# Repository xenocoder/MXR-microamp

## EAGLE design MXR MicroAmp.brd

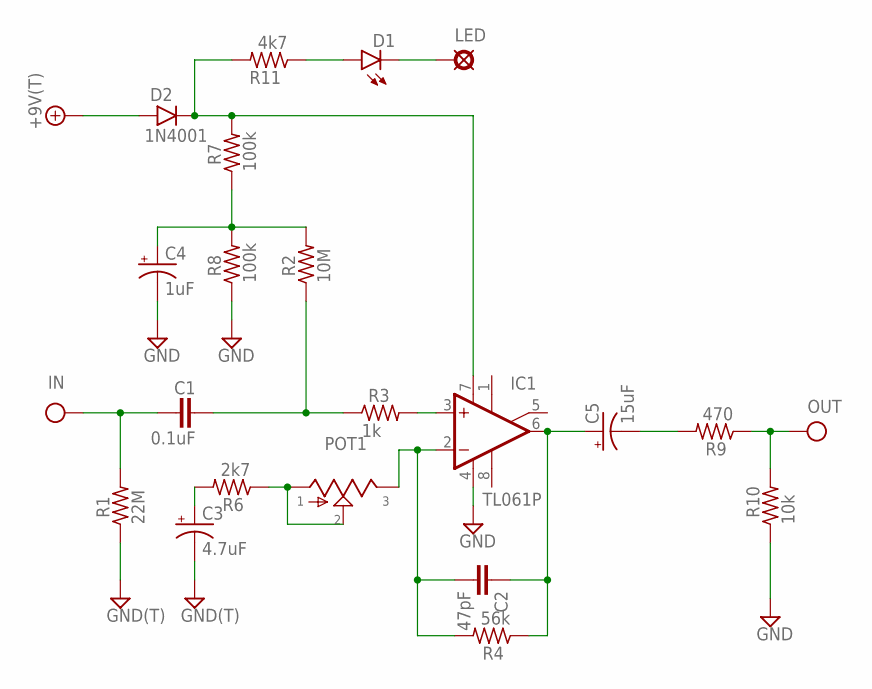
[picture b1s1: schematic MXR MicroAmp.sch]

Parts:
+9V: +9V(T); SQUARE
C1: 0.1uF; 072X025
C2: 47pF; 050X030_025
C3: 4.7uF; 044A
C4: 1uF; 044A
C5: 15uF; 063_025
D1: LED3MM
D2: 1N4001; DO41-1
G: GND(T); SQUARE
GND: GND(T); SQUARE
IC1: TL061P; DIL08
IN: IN(T); SQUARE
LED: LED; SQUARE
OUT: OUT(T); SQUARE
POT1: 9MMPOT_9MM_HOLES; POT_9MM_HOLES
R1: 22M; R0204/2
R2: 10M; R0204/2
R3: 1k; R0204/2
R4: 56k; R0204/2
R6: 2k7; R0204/2
R7, R8: 100k; R0204/2
R9: 470; R0204/2
R10: 10k; R0204/2
R11: 4k7; R0204/2

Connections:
+9V: +9V.1, D2.A
GND: C3.2 (-), C4.2 (-), G.1, GND.1, IC1.4 (V-), R1.1, R8.1, R10.1
IN: C1.1, IN.1, R1.2
unnamed: C1.2, R2.1, R3.1
unnamed: D2.C, IC1.7 (V+), R7.2, R11.2
unnamed: C4.1 (+), R2.2, R7.1, R8.2
unnamed: IC1.3 (+IN), R3.2
unnamed: C2.2, IC1.2 (-IN), POT1.P$3, R4.2
unnamed: POT1.P$1, POT1.P$2, R6.1
unnamed: C3.1 (+), R6.2
unnamed: C2.1, C5.+, IC1.6 (OUT), R4.1
unnamed: D1.A, R11.1
unnamed: D1.K (C), LED.1
unnamed: C5.-, R9.2
OUT: OUT.1, R9.1, R10.2

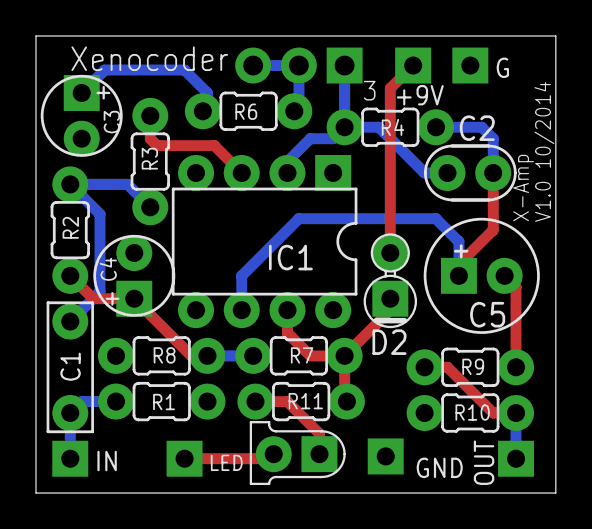
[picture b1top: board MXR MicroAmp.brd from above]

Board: 2 copper layers, 28.9 x 25.4 mm, 25 parts (0 on the bottom side), 15 nets.

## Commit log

2015-10-08 Initial upload
